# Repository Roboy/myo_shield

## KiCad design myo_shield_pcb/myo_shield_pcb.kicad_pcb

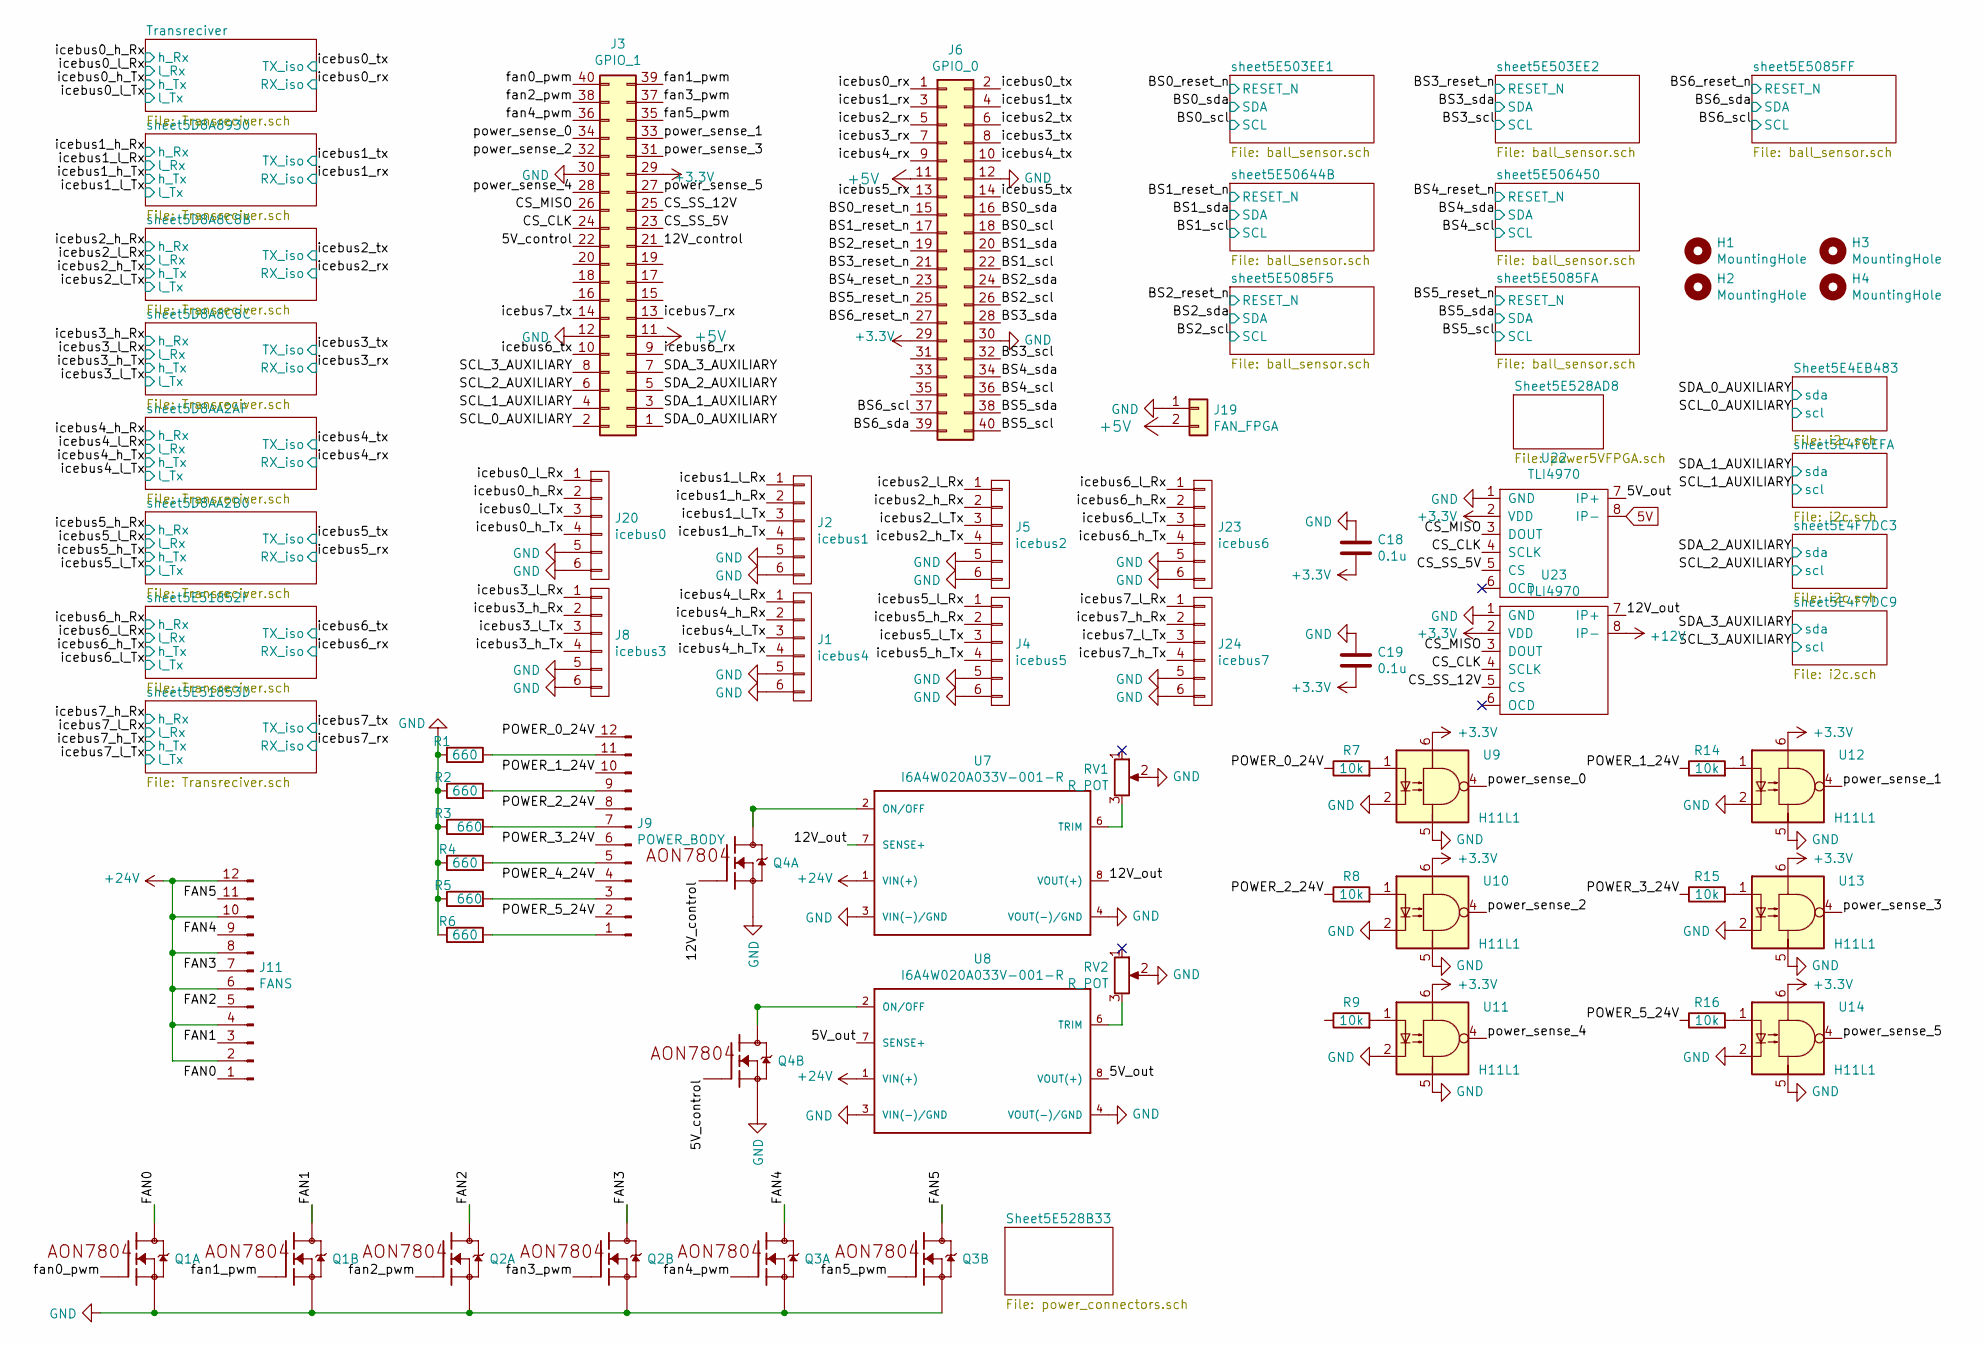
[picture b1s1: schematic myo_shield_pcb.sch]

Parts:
C18, C19: 0.1u; C_0402_1005Metric
H1, H2, H3, H4: MountingHole; MountingHole_3.2mm_M3
J1: icebus4; TE-Connectivity_Micro-Match_connector_02x03_Pitch_1.27mm
J2: icebus1; TE-Connectivity_Micro-Match_connector_02x03_Pitch_1.27mm
J3: GPIO_1; PinHeader_2x20_P2.54mm_Vertical
J4: icebus5; TE-Connectivity_Micro-Match_connector_02x03_Pitch_1.27mm
J5: icebus2; TE-Connectivity_Micro-Match_connector_02x03_Pitch_1.27mm
J6: GPIO_0; PinHeader_2x20_P2.54mm_Vertical
J8: icebus3; TE-Connectivity_Micro-Match_connector_02x03_Pitch_1.27mm
J9: POWER_BODY; PinHeader_2x06_P2.54mm_Vertical
J11: FANS; PinHeader_2x06_P2.54mm_Vertical
J19: FAN_FPGA; PinHeader_1x02_P2.54mm_Vertical
J20: icebus0; TE-Connectivity_Micro-Match_connector_02x03_Pitch_1.27mm
J23: icebus6; TE-Connectivity_Micro-Match_connector_02x03_Pitch_1.27mm
J24: icebus7; TE-Connectivity_Micro-Match_connector_02x03_Pitch_1.27mm
Q1, Q2, Q3, Q4: AON7804; DFN3X3
R1, R2, R3, R4, R5, R6: 660; R_0402_1005Metric
R7, R8, R9, R14, R15, R16: 10k; R_0402_1005Metric
RV1, RV2: R_POT; Potentiometer_Bourns_3214X_Vertical
U7, U8: I6A4W020A033V-001-R; TDK-LAMBDA_I6A4W020A033V-001-R
U9, U10, U11, U12, U13, U14: H11L1; DIL6-SMD
U22, U23: TLI4970

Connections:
5V: U22.8 (IP-); also elsewhere on the board
+3V3: C18.2, C19.2, J3.29, J6.29, U9.6, U10.6, U11.6, U12.6, U13.6, U14.6, U22.2 (VDD), U23.2 (VDD); also elsewhere on the board
+5V: J3.11, J6.11, J19.2; also elsewhere on the board
+12V: U23.8 (IP-); also elsewhere on the board
+24V: J11.2, J11.4, J11.6, J11.8, J11.10, J11.12, U7.1 (VIN(+)), U8.1 (VIN(+)); also elsewhere on the board
/5V_control: J3.22, Q4.G2 (G)
/5V_out: U8.7 (SENSE+), U8.8 (VOUT(+)), U22.7 (IP+)
/12V_control: J3.21, Q4.G1 (G)
/12V_out: U7.7 (SENSE+), U7.8 (VOUT(+)), U23.7 (IP+)
/BS0_reset_n: J6.15; also elsewhere on the board
/BS0_scl: J6.18; also elsewhere on the board
/BS0_sda: J6.16; also elsewhere on the board
/BS1_reset_n: J6.17; also elsewhere on the board
/BS1_scl: J6.22; also elsewhere on the board
/BS1_sda: J6.20; also elsewhere on the board
/BS2_reset_n: J6.19; also elsewhere on the board
/BS2_scl: J6.26; also elsewhere on the board
/BS2_sda: J6.24; also elsewhere on the board
/BS3_reset_n: J6.21; also elsewhere on the board
/BS3_scl: J6.32; also elsewhere on the board
/BS3_sda: J6.28; also elsewhere on the board
/BS4_reset_n: J6.23; also elsewhere on the board
/BS4_scl: J6.36; also elsewhere on the board
/BS4_sda: J6.34; also elsewhere on the board
/BS5_reset_n: J6.25; also elsewhere on the board
/BS5_scl: J6.40; also elsewhere on the board
/BS5_sda: J6.38; also elsewhere on the board
/BS6_reset_n: J6.27; also elsewhere on the board
/BS6_scl: J6.37; also elsewhere on the board
/BS6_sda: J6.39; also elsewhere on the board
/CS_CLK: J3.24, U22.4 (SCLK), U23.4 (SCLK)
/CS_MISO: J3.26, U22.3 (DOUT), U23.3 (DOUT)
/CS_SS_5V: J3.23, U22.5 (CS)
/CS_SS_12V: J3.25, U23.5 (CS)
/FAN0: J11.1, Q1.D1 (D), Q1.D1A (D1)
/FAN1: J11.3, Q1.D2 (D), Q1.D2A (D1)
/FAN2: J11.5, Q2.D1 (D), Q2.D1A (D1)
/FAN3: J11.7, Q2.D2 (D), Q2.D2A (D1)
/FAN4: J11.9, Q3.D1 (D), Q3.D1A (D1)
/FAN5: J11.11, Q3.D2 (D), Q3.D2A (D1)
/POWER_0_24V: J9.12, R7.1
/POWER_1_24V: J9.10, R14.1
/POWER_2_24V: J9.8, R8.1
/POWER_3_24V: J9.6, R15.1
/POWER_4_24V: J9.4
/POWER_5_24V: J9.2, R16.1
/SCL_0_AUXILIARY: J3.2; also elsewhere on the board
/SCL_1_AUXILIARY: J3.4; also elsewhere on the board
/SCL_2_AUXILIARY: J3.6; also elsewhere on the board
/SCL_3_AUXILIARY: J3.8; also elsewhere on the board
/SDA_0_AUXILIARY: J3.1; also elsewhere on the board
/SDA_1_AUXILIARY: J3.3; also elsewhere on the board
/SDA_2_AUXILIARY: J3.5; also elsewhere on the board
/SDA_3_AUXILIARY: J3.7; also elsewhere on the board
/fan0_pwm: J3.40, Q1.G1 (G)
/fan1_pwm: J3.39, Q1.G2 (G)
/fan2_pwm: J3.38, Q2.G1 (G)
/fan3_pwm: J3.37, Q2.G2 (G)
/fan4_pwm: J3.36, Q3.G1 (G)
/fan5_pwm: J3.35, Q3.G2 (G)
/icebus0_h_Rx: J20.2; also elsewhere on the board
/icebus0_h_Tx: J20.4; also elsewhere on the board
/icebus0_l_Rx: J20.1; also elsewhere on the board
/icebus0_l_Tx: J20.3; also elsewhere on the board
/icebus0_rx: J6.1; also elsewhere on the board
/icebus0_tx: J6.2; also elsewhere on the board
/icebus1_h_Rx: J2.2; also elsewhere on the board
/icebus1_h_Tx: J2.4; also elsewhere on the board
/icebus1_l_Rx: J2.1; also elsewhere on the board
/icebus1_l_Tx: J2.3; also elsewhere on the board
/icebus1_rx: J6.3; also elsewhere on the board
/icebus1_tx: J6.4; also elsewhere on the board
/icebus2_h_Rx: J5.2; also elsewhere on the board
/icebus2_h_Tx: J5.4; also elsewhere on the board
/icebus2_l_Rx: J5.1; also elsewhere on the board
/icebus2_l_Tx: J5.3; also elsewhere on the board
/icebus2_rx: J6.5; also elsewhere on the board
/icebus2_tx: J6.6; also elsewhere on the board
/icebus3_h_Rx: J8.2; also elsewhere on the board
/icebus3_h_Tx: J8.4; also elsewhere on the board
/icebus3_l_Rx: J8.1; also elsewhere on the board
/icebus3_l_Tx: J8.3; also elsewhere on the board
/icebus3_rx: J6.7; also elsewhere on the board
/icebus3_tx: J6.8; also elsewhere on the board
/icebus4_h_Rx: J1.2; also elsewhere on the board
/icebus4_h_Tx: J1.4; also elsewhere on the board
/icebus4_l_Rx: J1.1; also elsewhere on the board
/icebus4_l_Tx: J1.3; also elsewhere on the board
/icebus4_rx: J6.9; also elsewhere on the board
/icebus4_tx: J6.10; also elsewhere on the board
/icebus5_h_Rx: J4.2; also elsewhere on the board
/icebus5_h_Tx: J4.4; also elsewhere on the board
/icebus5_l_Rx: J4.1; also elsewhere on the board
/icebus5_l_Tx: J4.3; also elsewhere on the board
/icebus5_rx: J6.13; also elsewhere on the board
/icebus5_tx: J6.14; also elsewhere on the board
/icebus6_h_Rx: J23.2; also elsewhere on the board
/icebus6_h_Tx: J23.4; also elsewhere on the board
/icebus6_l_Rx: J23.1; also elsewhere on the board
/icebus6_l_Tx: J23.3; also elsewhere on the board
/icebus6_rx: J3.9; also elsewhere on the board
/icebus6_tx: J3.10; also elsewhere on the board
/icebus7_h_Rx: J24.2; also elsewhere on the board
/icebus7_h_Tx: J24.4; also elsewhere on the board
/icebus7_l_Rx: J24.1; also elsewhere on the board
/icebus7_l_Tx: J24.3; also elsewhere on the board
/icebus7_rx: J3.13; also elsewhere on the board
/icebus7_tx: J3.14; also elsewhere on the board
/power_sense_0: J3.34, U9.4
/power_sense_1: J3.33, U12.4
/power_sense_2: J3.32, U10.4
/power_sense_3: J3.31, U13.4
/power_sense_4: J3.28, U11.4
/power_sense_5: J3.27, U14.4
GND: C18.1, C19.1, J1.5, J1.6, J2.5, J2.6, J3.12, J3.30, J4.5, J4.6, J5.5, J5.6, J6.12, J6.30, J8.5, J8.6, J19.1, J20.5, J20.6, J23.5, J23.6, J24.5, J24.6, Q1.S1 (S), Q1.S2 (S), Q2.S1 (S), Q2.S2 (S), Q3.S1 (S), Q3.S2 (S), Q4.S1 (S), Q4.S2 (S), R1.2, R2.1, R3.1, R4.1, R5.1, R6.1, RV1.2, RV2.2, U7.3 (VIN(-)/GND), U7.4 (VOUT(-)/GND), U8.3 (VIN(-)/GND), U8.4 (VOUT(-)/GND), U9.2, U9.5, U10.2, U10.5, U11.2, U11.5, U12.2, U12.5, U13.2, U13.5, U14.2, U14.5, U22.1 (GND), U23.1 (GND); also elsewhere on the board
unnamed: J9.1, R6.2
unnamed: J9.3, R5.2
unnamed: J9.5, R4.2
unnamed: J9.7, R3.2
unnamed: J9.9, R2.2
unnamed: J9.11, R1.1
unnamed: Q4.D1 (D), Q4.D1A (D1), U7.2 (ON/OFF)
unnamed: Q4.D2 (D), Q4.D2A (D1), U8.2 (ON/OFF)
unnamed: R7.2, U9.1
unnamed: R8.2, U10.1
unnamed: R9.2, U11.1
unnamed: R14.2, U12.1
unnamed: R15.2, U13.1
unnamed: R16.2, U14.1
unnamed: RV1.3, U7.6 (TRIM)
unnamed: RV2.3, U8.6 (TRIM)

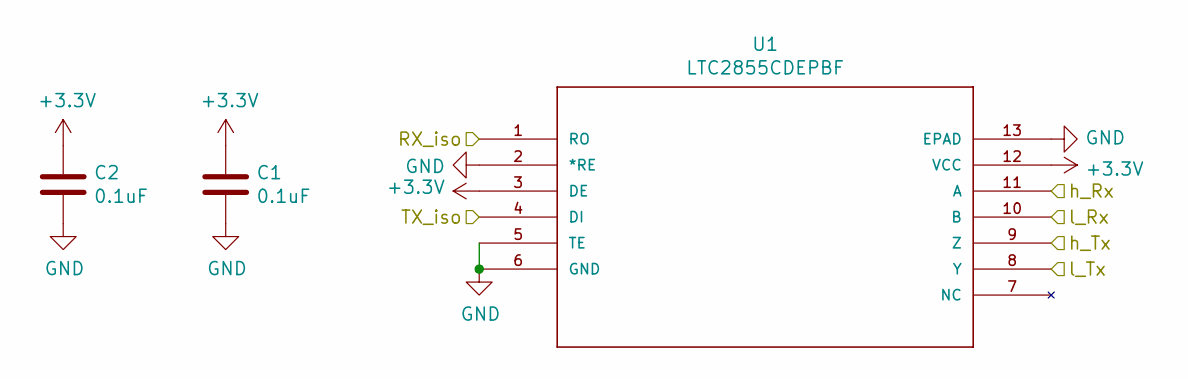
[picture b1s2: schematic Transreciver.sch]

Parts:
C1, C2: 0.1uF; C_0402_1005Metric
U1: LTC2855CDEPBF; ltc2855

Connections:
+3V3: C1.1, C2.1, U1.3 (DE), U1.12 (VCC); also elsewhere on the board
/icebus0_h_Rx: U1.11 (A); also elsewhere on the board
/icebus0_h_Tx: U1.9 (Z); also elsewhere on the board
/icebus0_l_Rx: U1.10 (B); also elsewhere on the board
/icebus0_l_Tx: U1.8 (Y); also elsewhere on the board
/icebus0_rx: U1.1 (RO); also elsewhere on the board
/icebus0_tx: U1.4 (DI); also elsewhere on the board
GND: C1.2, C2.2, U1.2 (*RE), U1.5 (TE), U1.6 (GND), U1.13 (EPAD); also elsewhere on the board

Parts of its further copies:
C3, C4, C5, C6, C7, C8, C9, C10, C11, C12, C20, C21, C22, C23, C24, C25, C26, C27: 0.1uF; C_0402_1005Metric
U2, U3, U4, U5, U6, U24, U25, U26, U27: LTC2855CDEPBF; ltc2855

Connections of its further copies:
+3V3: C3.1, C4.1, C5.1, C6.1, C7.1, C8.1, C9.1, C10.1, C11.1, C12.1, C20.1, C21.1, C22.1, C23.1, U2.3 (DE), U2.12 (VCC), U3.3 (DE), U3.12 (VCC), U4.3 (DE), U4.12 (VCC), U5.3 (DE), U5.12 (VCC), U6.3 (DE), U6.12 (VCC), U24.3 (DE), U24.12 (VCC), U25.3 (DE), U25.12 (VCC); also elsewhere on the board
/icebus1_h_Rx: U2.11 (A); also elsewhere on the board
/icebus1_h_Tx: U2.9 (Z); also elsewhere on the board
/icebus1_l_Rx: U2.10 (B); also elsewhere on the board
/icebus1_l_Tx: U2.8 (Y); also elsewhere on the board
/icebus1_rx: U2.1 (RO); also elsewhere on the board
/icebus1_tx: U2.4 (DI); also elsewhere on the board
/icebus2_h_Rx: U3.11 (A); also elsewhere on the board
/icebus2_h_Tx: U3.9 (Z); also elsewhere on the board
/icebus2_l_Rx: U3.10 (B); also elsewhere on the board
/icebus2_l_Tx: U3.8 (Y); also elsewhere on the board
/icebus2_rx: U3.1 (RO); also elsewhere on the board
/icebus2_tx: U3.4 (DI); also elsewhere on the board
/icebus3_h_Rx: U4.11 (A); also elsewhere on the board
/icebus3_h_Tx: U4.9 (Z); also elsewhere on the board
/icebus3_l_Rx: U4.10 (B); also elsewhere on the board
/icebus3_l_Tx: U4.8 (Y); also elsewhere on the board
/icebus3_rx: U4.1 (RO); also elsewhere on the board
/icebus3_tx: U4.4 (DI); also elsewhere on the board
/icebus4_h_Rx: U5.11 (A); also elsewhere on the board
/icebus4_h_Tx: U5.9 (Z); also elsewhere on the board
/icebus4_l_Rx: U5.10 (B); also elsewhere on the board
/icebus4_l_Tx: U5.8 (Y); also elsewhere on the board
/icebus4_rx: U5.1 (RO); also elsewhere on the board
/icebus4_tx: U5.4 (DI); also elsewhere on the board
/icebus5_h_Rx: U6.11 (A); also elsewhere on the board
/icebus5_h_Tx: U6.9 (Z); also elsewhere on the board
/icebus5_l_Rx: U6.10 (B); also elsewhere on the board
/icebus5_l_Tx: U6.8 (Y); also elsewhere on the board
/icebus5_rx: U6.1 (RO); also elsewhere on the board
/icebus5_tx: U6.4 (DI); also elsewhere on the board
/icebus6_h_Rx: U24.11 (A); also elsewhere on the board
/icebus6_h_Tx: U24.9 (Z); also elsewhere on the board
/icebus6_l_Rx: U24.10 (B); also elsewhere on the board
/icebus6_l_Tx: U24.8 (Y); also elsewhere on the board
/icebus6_rx: U24.1 (RO); also elsewhere on the board
/icebus6_tx: U24.4 (DI); also elsewhere on the board
/icebus7_h_Rx: U25.11 (A); also elsewhere on the board
/icebus7_h_Tx: U25.9 (Z); also elsewhere on the board
/icebus7_l_Rx: U25.10 (B); also elsewhere on the board
/icebus7_l_Tx: U25.8 (Y); also elsewhere on the board
/icebus7_rx: U25.1 (RO); also elsewhere on the board
/icebus7_tx: U25.4 (DI); also elsewhere on the board
GND: C3.2, C4.2, C5.2, C6.2, C7.2, C8.2, C9.2, C10.2, C11.2, C12.2, C20.2, C21.2, C22.2, C23.2, U2.2 (*RE), U2.5 (TE), U2.6 (GND), U2.13 (EPAD), U3.2 (*RE), U3.5 (TE), U3.6 (GND), U3.13 (EPAD), U4.2 (*RE), U4.5 (TE), U4.6 (GND), U4.13 (EPAD), U5.2 (*RE), U5.5 (TE), U5.6 (GND), U5.13 (EPAD), U6.2 (*RE), U6.5 (TE), U6.6 (GND), U6.13 (EPAD), U24.2 (*RE), U24.5 (TE), U24.6 (GND), U24.13 (EPAD), U25.2 (*RE), U25.5 (TE), U25.6 (GND), U25.13 (EPAD); also elsewhere on the board

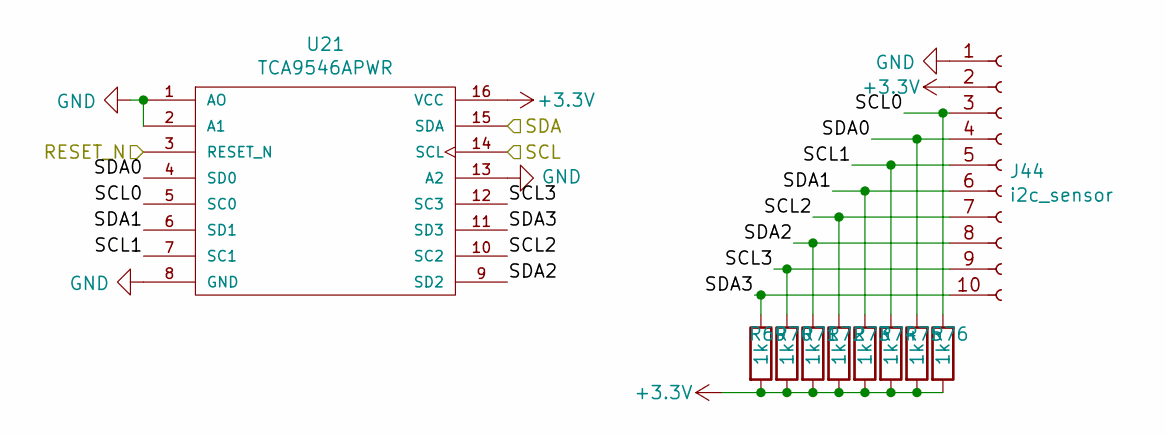
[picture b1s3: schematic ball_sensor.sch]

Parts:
J10: i2c_sensor; TE-Connectivity_Micro-Match_connector_02x05_Pitch_1.27mm
R21, R22, R23, R24, R25, R26, R27, R28: 1k; R_0402_1005Metric
U15: TCA9546APWR; SOP65P640X120-16N

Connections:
+3V3: J10.2, R21.2, R22.2, R23.2, R24.2, R25.2, R26.2, R27.2, R28.2, U15.16 (VCC); also elsewhere on the board
/BS0_reset_n: U15.3 (RESET_N); also elsewhere on the board
/BS0_scl: U15.14 (SCL); also elsewhere on the board
/BS0_sda: U15.15 (SDA); also elsewhere on the board
/sheet5E503EE1/SCL0: J10.3, R28.1, U15.5 (SC0)
/sheet5E503EE1/SCL1: J10.5, R26.1, U15.7 (SC1)
/sheet5E503EE1/SCL2: J10.7, R24.1, U15.10 (SC2)
/sheet5E503EE1/SCL3: J10.9, R22.1, U15.12 (SC3)
/sheet5E503EE1/SDA0: J10.4, R27.1, U15.4 (SD0)
/sheet5E503EE1/SDA1: J10.6, R25.1, U15.6 (SD1)
/sheet5E503EE1/SDA2: J10.8, R23.1, U15.9 (SD2)
/sheet5E503EE1/SDA3: J10.10, R21.1, U15.11 (SD3)
GND: J10.1, U15.1 (AO), U15.2 (A1), U15.8 (GND), U15.13 (A2); also elsewhere on the board

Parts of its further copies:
J12, J13, J14, J15, J43, J44: i2c_sensor; TE-Connectivity_Micro-Match_connector_02x05_Pitch_1.27mm
R29, R30, R31, R32, R33, R34, R35, R36, R37, R38, R39, R40, R41, R42, R43, R44, R45, R46, R47, R48, R49, R50, R51, R52, R53, R54, R55, R56, R57, R58, R59, R60, R61, R62, R63, R64, R65, R66, R67, R68, R69, R70, R71, R72, R73, R74, R75, R76: 1k; R_0402_1005Metric
U16, U17, U18, U19, U20, U21: TCA9546APWR; SOP65P640X120-16N

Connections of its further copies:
+3V3: J12.2, J13.2, J14.2, J15.2, J43.2, J44.2, R29.2, R30.2, R31.2, R32.2, R33.2, R34.2, R35.2, R36.2, R37.2, R38.2, R39.2, R40.2, R41.2, R42.2, R43.2, R44.2, R45.2, R46.2, R47.2, R48.2, R49.2, R50.2, R51.2, R52.2, R53.2, R54.2, R55.2, R56.2, R57.2, R58.2, R59.2, R60.2, R61.2, R62.2, R63.2, R64.2, R65.2, R66.2, R67.2, R68.2, R69.2, R70.2, R71.2, R72.2, R73.2, R74.2, R75.2, R76.2, U16.16 (VCC), U17.16 (VCC), U18.16 (VCC), U19.16 (VCC), U20.16 (VCC), U21.16 (VCC); also elsewhere on the board
/BS1_reset_n: U17.3 (RESET_N); also elsewhere on the board
/BS1_scl: U17.14 (SCL); also elsewhere on the board
/BS1_sda: U17.15 (SDA); also elsewhere on the board
/BS2_reset_n: U19.3 (RESET_N); also elsewhere on the board
/BS2_scl: U19.14 (SCL); also elsewhere on the board
/BS2_sda: U19.15 (SDA); also elsewhere on the board
/BS3_reset_n: U16.3 (RESET_N); also elsewhere on the board
/BS3_scl: U16.14 (SCL); also elsewhere on the board
/BS3_sda: U16.15 (SDA); also elsewhere on the board
/BS4_reset_n: U18.3 (RESET_N); also elsewhere on the board
/BS4_scl: U18.14 (SCL); also elsewhere on the board
/BS4_sda: U18.15 (SDA); also elsewhere on the board
/BS5_reset_n: U20.3 (RESET_N); also elsewhere on the board
/BS5_scl: U20.14 (SCL); also elsewhere on the board
/BS5_sda: U20.15 (SDA); also elsewhere on the board
/BS6_reset_n: U21.3 (RESET_N); also elsewhere on the board
/BS6_scl: U21.14 (SCL); also elsewhere on the board
/BS6_sda: U21.15 (SDA); also elsewhere on the board
/sheet5E503EE2/SCL0: J12.3, R36.1, U16.5 (SC0)
/sheet5E503EE2/SCL1: J12.5, R34.1, U16.7 (SC1)
/sheet5E503EE2/SCL2: J12.7, R32.1, U16.10 (SC2)
/sheet5E503EE2/SCL3: J12.9, R30.1, U16.12 (SC3)
/sheet5E503EE2/SDA0: J12.4, R35.1, U16.4 (SD0)
/sheet5E503EE2/SDA1: J12.6, R33.1, U16.6 (SD1)
/sheet5E503EE2/SDA2: J12.8, R31.1, U16.9 (SD2)
/sheet5E503EE2/SDA3: J12.10, R29.1, U16.11 (SD3)
/sheet5E5085F5/SCL0: J15.3, R60.1, U19.5 (SC0)
/sheet5E5085F5/SCL1: J15.5, R58.1, U19.7 (SC1)
/sheet5E5085F5/SCL2: J15.7, R56.1, U19.10 (SC2)
/sheet5E5085F5/SCL3: J15.9, R54.1, U19.12 (SC3)
/sheet5E5085F5/SDA0: J15.4, R59.1, U19.4 (SD0)
/sheet5E5085F5/SDA1: J15.6, R57.1, U19.6 (SD1)
/sheet5E5085F5/SDA2: J15.8, R55.1, U19.9 (SD2)
/sheet5E5085F5/SDA3: J15.10, R53.1, U19.11 (SD3)
/sheet5E5085FA/SCL0: J43.3, R68.1, U20.5 (SC0)
/sheet5E5085FA/SCL1: J43.5, R66.1, U20.7 (SC1)
/sheet5E5085FA/SCL2: J43.7, R64.1, U20.10 (SC2)
/sheet5E5085FA/SCL3: J43.9, R62.1, U20.12 (SC3)
/sheet5E5085FA/SDA0: J43.4, R67.1, U20.4 (SD0)
/sheet5E5085FA/SDA1: J43.6, R65.1, U20.6 (SD1)
/sheet5E5085FA/SDA2: J43.8, R63.1, U20.9 (SD2)
/sheet5E5085FA/SDA3: J43.10, R61.1, U20.11 (SD3)
/sheet5E5085FF/SCL0: J44.3, R76.1, U21.5 (SC0)
/sheet5E5085FF/SCL1: J44.5, R74.1, U21.7 (SC1)
/sheet5E5085FF/SCL2: J44.7, R72.1, U21.10 (SC2)
/sheet5E5085FF/SCL3: J44.9, R70.1, U21.12 (SC3)
/sheet5E5085FF/SDA0: J44.4, R75.1, U21.4 (SD0)
/sheet5E5085FF/SDA1: J44.6, R73.1, U21.6 (SD1)
/sheet5E5085FF/SDA2: J44.8, R71.1, U21.9 (SD2)
/sheet5E5085FF/SDA3: J44.10, R69.1, U21.11 (SD3)
/sheet5E50644B/SCL0: J13.3, R44.1, U17.5 (SC0)
/sheet5E50644B/SCL1: J13.5, R42.1, U17.7 (SC1)
/sheet5E50644B/SCL2: J13.7, R40.1, U17.10 (SC2)
/sheet5E50644B/SCL3: J13.9, R38.1, U17.12 (SC3)
/sheet5E50644B/SDA0: J13.4, R43.1, U17.4 (SD0)
/sheet5E50644B/SDA1: J13.6, R41.1, U17.6 (SD1)
/sheet5E50644B/SDA2: J13.8, R39.1, U17.9 (SD2)
/sheet5E50644B/SDA3: J13.10, R37.1, U17.11 (SD3)
/sheet5E506450/SCL0: J14.3, R52.1, U18.5 (SC0)
/sheet5E506450/SCL1: J14.5, R50.1, U18.7 (SC1)
/sheet5E506450/SCL2: J14.7, R48.1, U18.10 (SC2)
/sheet5E506450/SCL3: J14.9, R46.1, U18.12 (SC3)
/sheet5E506450/SDA0: J14.4, R51.1, U18.4 (SD0)
/sheet5E506450/SDA1: J14.6, R49.1, U18.6 (SD1)
/sheet5E506450/SDA2: J14.8, R47.1, U18.9 (SD2)
/sheet5E506450/SDA3: J14.10, R45.1, U18.11 (SD3)
GND: J12.1, J13.1, J14.1, J15.1, J43.1, J44.1, U16.1 (AO), U16.2 (A1), U16.8 (GND), U16.13 (A2), U17.1 (AO), U17.2 (A1), U17.8 (GND), U17.13 (A2), U18.1 (AO), U18.2 (A1), U18.8 (GND), U18.13 (A2), U19.1 (AO), U19.2 (A1), U19.8 (GND), U19.13 (A2), U20.1 (AO), U20.2 (A1), U20.8 (GND), U20.13 (A2), U21.1 (AO), U21.2 (A1), U21.8 (GND), U21.13 (A2); also elsewhere on the board

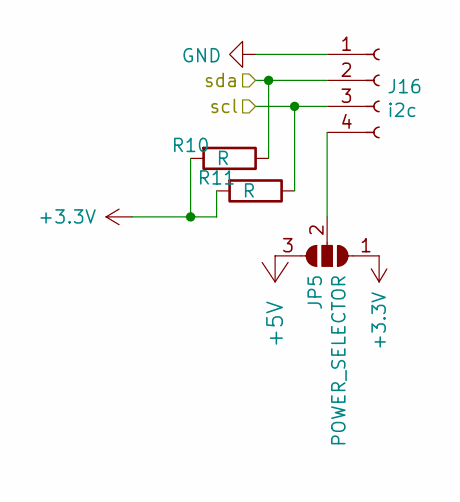
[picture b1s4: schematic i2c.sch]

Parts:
J16: i2c; TE-Connectivity_Micro-Match_connector_02x02_Pitch_1.27mm
JP5: POWER_SELECTOR; Solder_Bridge_3_0402
R10, R11: R; R_0402_1005Metric

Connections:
+3V3: JP5.1 (A), R10.2, R11.2; also elsewhere on the board
+5V: JP5.3 (B); also elsewhere on the board
/SCL_0_AUXILIARY: J16.3, R11.1; also elsewhere on the board
/SDA_0_AUXILIARY: J16.2, R10.1; also elsewhere on the board
GND: J16.1; also elsewhere on the board
unnamed: J16.4, JP5.2 (C)

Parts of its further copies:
J17, J18, J21: i2c; TE-Connectivity_Micro-Match_connector_02x02_Pitch_1.27mm
JP6, JP7, JP8: POWER_SELECTOR; Solder_Bridge_3_0402
R12, R13, R17, R18, R19, R20: R; R_0402_1005Metric

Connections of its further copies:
+3V3: JP6.1 (A), JP7.1 (A), JP8.1 (A), R12.2, R13.2, R17.2, R18.2, R19.2, R20.2; also elsewhere on the board
+5V: JP6.3 (B), JP7.3 (B), JP8.3 (B); also elsewhere on the board
/SCL_1_AUXILIARY: J17.3, R13.1; also elsewhere on the board
/SCL_2_AUXILIARY: J18.3, R18.1; also elsewhere on the board
/SCL_3_AUXILIARY: J21.3, R20.1; also elsewhere on the board
/SDA_1_AUXILIARY: J17.2, R12.1; also elsewhere on the board
/SDA_2_AUXILIARY: J18.2, R17.1; also elsewhere on the board
/SDA_3_AUXILIARY: J21.2, R19.1; also elsewhere on the board
GND: J17.1, J18.1, J21.1; also elsewhere on the board
unnamed: J17.4, JP6.2 (C)
unnamed: J18.4, JP7.2 (C)
unnamed: J21.4, JP8.2 (C)

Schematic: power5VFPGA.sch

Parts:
C13, C14: 2.2uF; C_0603_1608Metric
C15: 5600pF; C_0402_1005Metric
C16: 0.1uF; C_0402_1005Metric
C17: 22uF; C_0805_2012Metric
L1: 10uH; XAL5050-103MEC
MAX1: MAX17632; QFN-16-1EP_3x3mm_Pitch0.5mm
TP1: TestPoint; TestPoint_Pad_D1.0mm

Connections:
+5V: C17.2, L1.1, MAX1.6, MAX1.9, TP1.1; also elsewhere on the board
+24V: C14.1, MAX1.1, MAX1.15, MAX1.16; also elsewhere on the board
GND: C13.2, C14.2, C15.2, C17.1, MAX1.3, MAX1.4, MAX1.13, MAX1.14; also elsewhere on the board
unnamed: C13.1, MAX1.2
unnamed: C15.1, MAX1.5
unnamed: C16.1, L1.2, MAX1.11, MAX1.12
unnamed: C16.2, MAX1.10

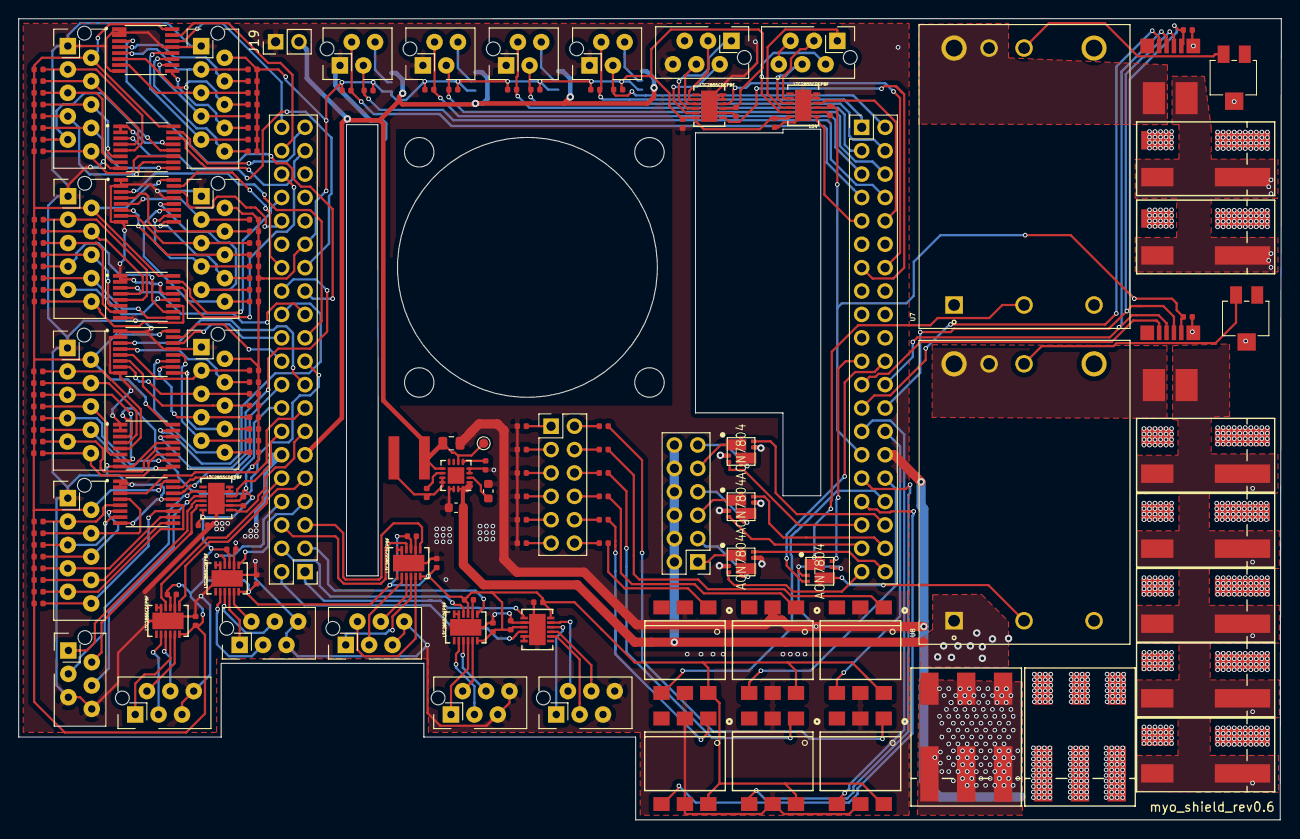
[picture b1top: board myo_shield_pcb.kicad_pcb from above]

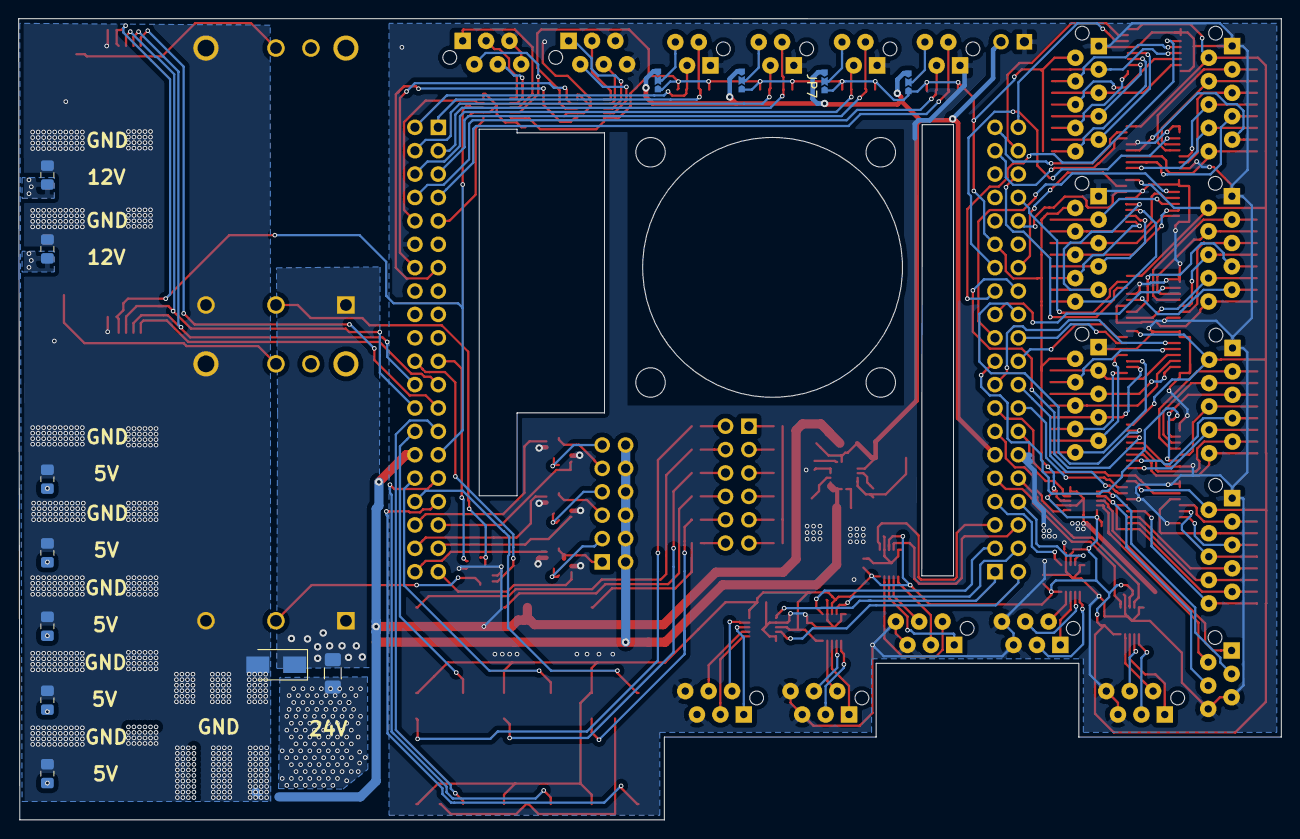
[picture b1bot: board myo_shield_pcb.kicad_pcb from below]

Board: 2 copper layers, 137.1 x 87.0 mm, 183 parts (13 on the bottom side), 195 nets.

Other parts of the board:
Co25, Co26, Co27, Co28, Co29, Co30, Co31: 10uF; C_0805_2012Metric_Pad1.15x1.40mm_HandSolder
Dsafe1: D; D_SMA
F1: Fuse; C_1206_3216Metric_Pad1.42x1.75mm_HandSolder
J25, J26, J27, J28, J29: 5V; Wago_2060_2_SMD
J30, J31: 12V; Wago_2060_2_SMD
J32: 24V; Wago_2060_3_SMD
J33: GND; Wago_2060_3_SMD

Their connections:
5V: Co25.1, Co26.1, Co27.1, Co28.1, Co29.1, J25.2, J26.2, J27.2, J28.2, J29.2; also elsewhere on the board
+12V: Co30.1, Co31.1, J30.2, J31.2; also elsewhere on the board
+24V: Dsafe1.1, F1.2; also elsewhere on the board
GND: Co25.2, Co26.2, Co27.2, Co28.2, Co29.2, Co30.2, Co31.2, Dsafe1.2, J25.1, J26.1, J27.1, J28.1, J29.1, J30.1, J31.1, J33.1, J33.2, J33.3; also elsewhere on the board
unnamed: F1.1, J32.1, J32.2, J32.3

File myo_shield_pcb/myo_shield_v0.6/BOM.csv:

Id,Designator,Package,Quantity,Price per unit,Designation,Supplier and ref
1,F1,C_1206_3216Metric_Pad1.42x1.75mm_HandSolder,1,0.98 €,Fuse,https://www.mouser.de/ProductDetail/Bel-Fuse/0685P9250-01?qs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
3,"Co31,Co30,Co29,Co28,Co27,Co26,Co25",C_0805_2012Metric_Pad1.15x1.40mm_HandSolder,7,0.14 €,10uF,https://www.mouser.de/ProductDetail/TDK/CGA4J1X7S1C106K125AE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
7,"C2,C1,C3,C4,C5,C6,C7,C8,C9,C10,C11,C12,C16,C18,C19,C20,C21,C22,C23",C_0402_1005Metric,19,0.01 €,0.1uF,
9,"U1,U2,U3,U4,U5,U6,U24,U25",ltc2855,8,2.46 €,LTC2855CDEPBF,https://www.mouser.de/ProductDetail/Analog-Devices-Linear-Te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
18,"J31,J30,J25,J26,J27,J28,J29",Wago_2060_2_SMD,7,0.67 €,12V,https://www.reichelt.com/de/en/smd-pcb-terminal-2-pole-rm-4-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
19,"Q1,Q2,Q3,Q4",DFN3X3,4,0.31 €,AON7804,https://www.digikey.de/product-detail/en/AON7804/785-1586-1-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
20,"R1,R2,R3,R4,R5,R6",R_0402_1005Metric,6,0.01 €,660,
21,"R7,R8,R9,R14,R15,R16",R_0402_1005Metric,6,0.01 €,10k,
22,"R10,R11,R12,R13,R17,R18,R19,R20",R_0402_1005Metric,8,0.01 €,1k,
23,"RV1,RV2",Potentiometer_Bourns_3214X_Vertical,2,2.94 €,R_POT,https://www.digikey.de/product-detail/en/3214X-1-203E/3214X-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
25,"U9,U10,U11,U12,U13,U14",DIL6-SMD,6,0.48 €,H11L1,https://www.digikey.de/product-detail/en/H11L1S(TA)/1080-120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
26,"J32,J33",Wago_2060_3_SMD,2,0.59 €,GND,https://www.reichelt.com/de/en/smd-pcb-terminal-3-pole-rm-4-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
27,"R21,R22,R23,R24,R25,R26,R27,R28,R29,R30,R31,R32,R33,R34,R35,R36,R37,R38,R39,R40,R41,R42,R43,R44,R45,R46,R47,R48,R49,R50,R51,R52,R53,R54,R55,R56,R57,R58,R59,R60,R61,R62,R63,R64,R65,R66,R67,R68,R69,R70,R71,R72,R73,R74,R75,R76",R_0402_1005Metric,56,0.01 €,1k,
28,"U15,U16,U17,U18,U19,U20,U21",SOP65P640X120-16N,7,1.03 €,TCA9546APWR,https://www.digikey.de/product-detail/en/TCA9546APWR/296-405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
30,"C13,C14",C_0603_1608Metric,2,0.15 €,2.2uF,https://www.mouser.de/ProductDetail/Murata-Electronics/GRM18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
31,C15,C_0402_1005Metric,1,0.01 €,5600pF,
32,C17,C_0805_2012Metric,1,0.86 €,22uF,https://www.mouser.de/ProductDetail/Murata-Electronics/GRM32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
33,L1,XAL5050-103MEC,1,2.49 €,10uH,https://www.mouser.de/ProductDetail/Coilcraft/XAL5050-103MEC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
34,MAX1,QFN-16-1EP_3x3mm_Pitch0.5mm,1,1.91 €,MAX17632,https://www.mouser.de/ProductDetail/Maxim-Integrated/MAX1763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
37,"U22,U23",TLI4970,2,6.64 €,TLI4970,https://www.mouser.de/ProductDetail/Infineon-Technologies/TL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
,,,total no parts:,Total price:,,
,,,147,64.51 €,,

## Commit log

2018-12-07 version 1
2018-12-07 rev0.1
2018-12-07 with pcb
2018-12-28 fixed small GND connection
2019-02-02 rev 0.2
2019-02-11 with fan control
2019-02-27 pcb almost done
2019-02-28 done
2019-02-28 correct path
2019-02-28 more labels
2019-05-10 draft for spi bus protection
2019-05-11 v0.3
2019-09-02 added RS485
2019-09-03 replaced 0402 footprint with the correct one, minor fixes
2019-09-23 draft
2019-09-23 with ice and i2c buses
2019-09-23 with icebus draft
2019-09-25 with 8 icebus and dedicated connectors for 3d magnetic sensor rings
2019-10-14 with updated image
2020-02-20 layout draft
2020-02-20 layput almost done
2020-02-21 moreprogress:
2020-02-25 layout done
2020-02-26 exported again
2020-03-05 added output Caps and input Fuse
2020-03-05 with bom
2020-03-10 fix fan mosfet
